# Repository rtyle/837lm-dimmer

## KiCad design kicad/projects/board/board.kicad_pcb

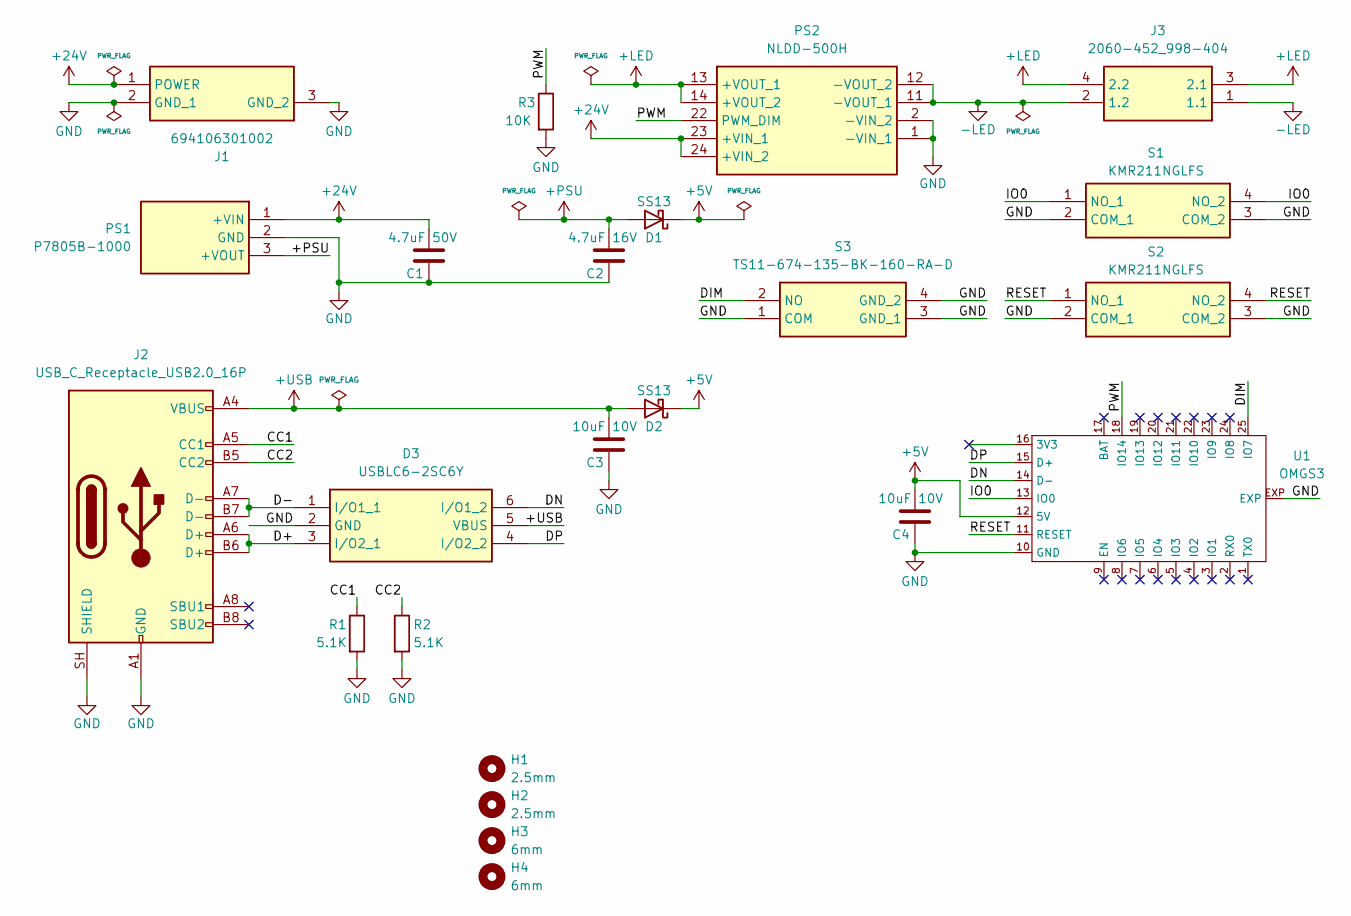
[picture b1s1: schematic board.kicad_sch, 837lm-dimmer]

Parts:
C1: 4.7uF 50V; C_1210_3225Metric; Manufacturer_Part_Number KAF32LR71H475KU; Mouser Part Number 581-KAF32LR71H475KU
C2: 4.7uF 16V; C_1210_3225Metric; Manufacturer_Part_Number KAF32KR71C475KU; Mouser Part Number 581-KAF32KR71C475KU
C3, C4: 10uF 10V; C_0805_2012Metric; Manufacturer_Part_Number C0805X106K8RAUTLR; Mouser Part Number 80-C0805X106K8RAUTLR
D1, D2: SS13; DIOM5227X250N; Manufacturer_Part_Number SS13; Mouser Part Number 512-SS13
D3: USBLC6-2SC6Y; SOT95P280X145-6N; Manufacturer_Part_Number USBLC6-2SC6Y; Mouser Part Number 511-USBLC6-2SC6Y
H1, H2: 2.5mm; MountingHole_2.5mm
H3, H4: 6mm; MountingHole_5.5mm
J1: 694106301002; Manufacturer_Part_Number 694106301002; Mouser Part Number 710-694106301002
J2: USB_C_Receptacle_USB2.0_16P; USB_C_Receptacle_GCT_USB4085; Manufacturer_Part_Number USB4085-GF-A; Mouser Part Number 640-USB4085-GF-A
J3: 2060-452_998-404; 2060452998404; Manufacturer_Part_Number 2060-452/998-404; Mouser Part Number 1089-2060452/998-404
PS1: P7805B-1000; P7805B1000; Manufacturer_Part_Number P7805B-1000; Mouser Part Number 490-P7805B-1000
PS2: NLDD-500H; NLDD500H; Manufacturer_Part_Number NLDD-500H; Mouser Part Number 709-NLDD-500H
R1, R2: 5.1K; R_0603_1608Metric; Manufacturer_Part_Number ERJ-3EKF5101V; Mouser Part Number 667-ERJ-3EKF5101V
R3: 10K; R_0603_1608Metric; Manufacturer_Part_Number ERJ-3EKF1002V; Mouser Part Number 667-ERJ-3EKF1002V
S1, S2: KMR211NGLFS; Manufacturer_Part_Number KMR211NGLFS; Mouser Part Number 611-KMR211NGLFS
S3: TS11-674-135-BK-160-RA-D; TS11674135BK160RAD; Manufacturer_Part_Number TS11-674-135-BK-160-RA-D; Mouser Part Number 179-TS11674135160RAD
U1: OMGS3; Manufacturer_Part_Number OMGS3; Mouser Part Number 392-OMGS3-01

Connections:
+5V: C4.2, D1.1 (K), D2.1 (K), U1.12 (5V)
+24V: C1.2, J1.1 (POWER), PS1.1 (+VIN), PS2.23 (+VIN_1), PS2.24 (+VIN_2)
+LED: J3.3 (2.1), J3.4 (2.2), PS2.13 (+VOUT_1), PS2.14 (+VOUT_2)
+PSU: C2.2, D1.2 (A), PS1.3 (+VOUT)
+USB: C3.2, D2.2 (A), D3.5 (VBUS), J2.A4 (VBUS), J2.A9 (VBUS), J2.B4 (VBUS), J2.B9 (VBUS)
-LED: J3.1 (1.1), J3.2 (1.2), PS2.11 (-VOUT_1), PS2.12 (-VOUT_2)
/CC1: J2.A5 (CC1), R1.1
/CC2: J2.B5 (CC2), R2.1
/D+: D3.3 (I/O2_1), J2.A6 (D+), J2.B6 (D+)
/D-: D3.1 (I/O1_1), J2.A7 (D-), J2.B7 (D-)
/DIM: S3.2 (NO), U1.25 (IO7)
/DN: D3.6 (I/O1_2), U1.14 (D-)
/DP: D3.4 (I/O2_2), U1.15 (D+)
/IO0: S1.1 (NO_1), S1.4 (NO_2), U1.13 (IO0)
/PWM: PS2.22 (PWM_DIM), R3.1, U1.18 (IO14)
/RESET: S2.1 (NO_1), S2.4 (NO_2), U1.11 (RESET)
GND: C1.1, C2.1, C3.1, C4.1, D3.2 (GND), J1.2 (GND_1), J1.3 (GND_2), J2.A1 (GND), J2.A12 (GND), J2.B1 (GND), J2.B12 (GND), J2.SH (SHIELD), PS1.2 (GND), PS2.1 (-VIN_1), PS2.2 (-VIN_2), R1.2, R2.2, R3.2, S1.2 (COM_1), S1.3 (COM_2), S2.2 (COM_1), S2.3 (COM_2), S3.1 (COM), S3.3 (GND_1), S3.4 (GND_2), U1.10 (GND), U1.EXP

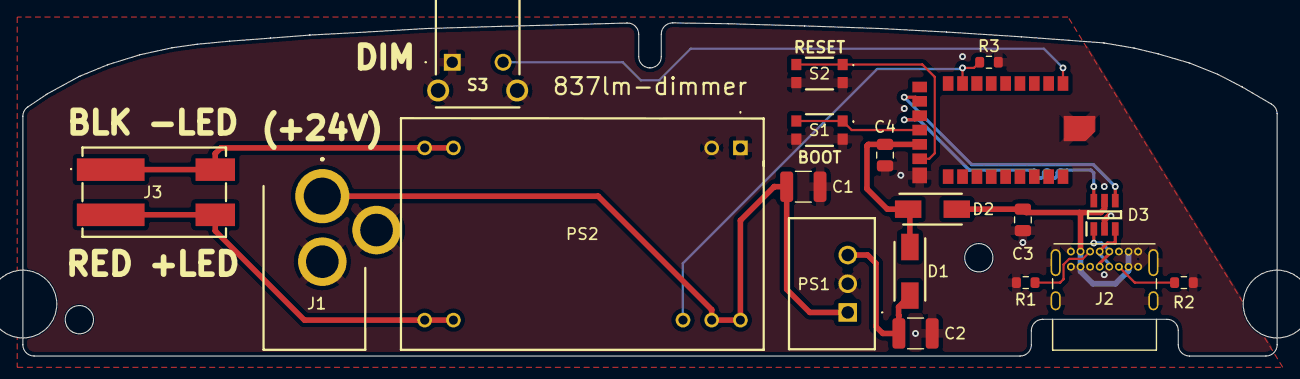
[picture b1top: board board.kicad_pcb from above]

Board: 4 copper layers, 111.0 x 29.5 mm, 23 parts (0 on the bottom side), 17 nets.
